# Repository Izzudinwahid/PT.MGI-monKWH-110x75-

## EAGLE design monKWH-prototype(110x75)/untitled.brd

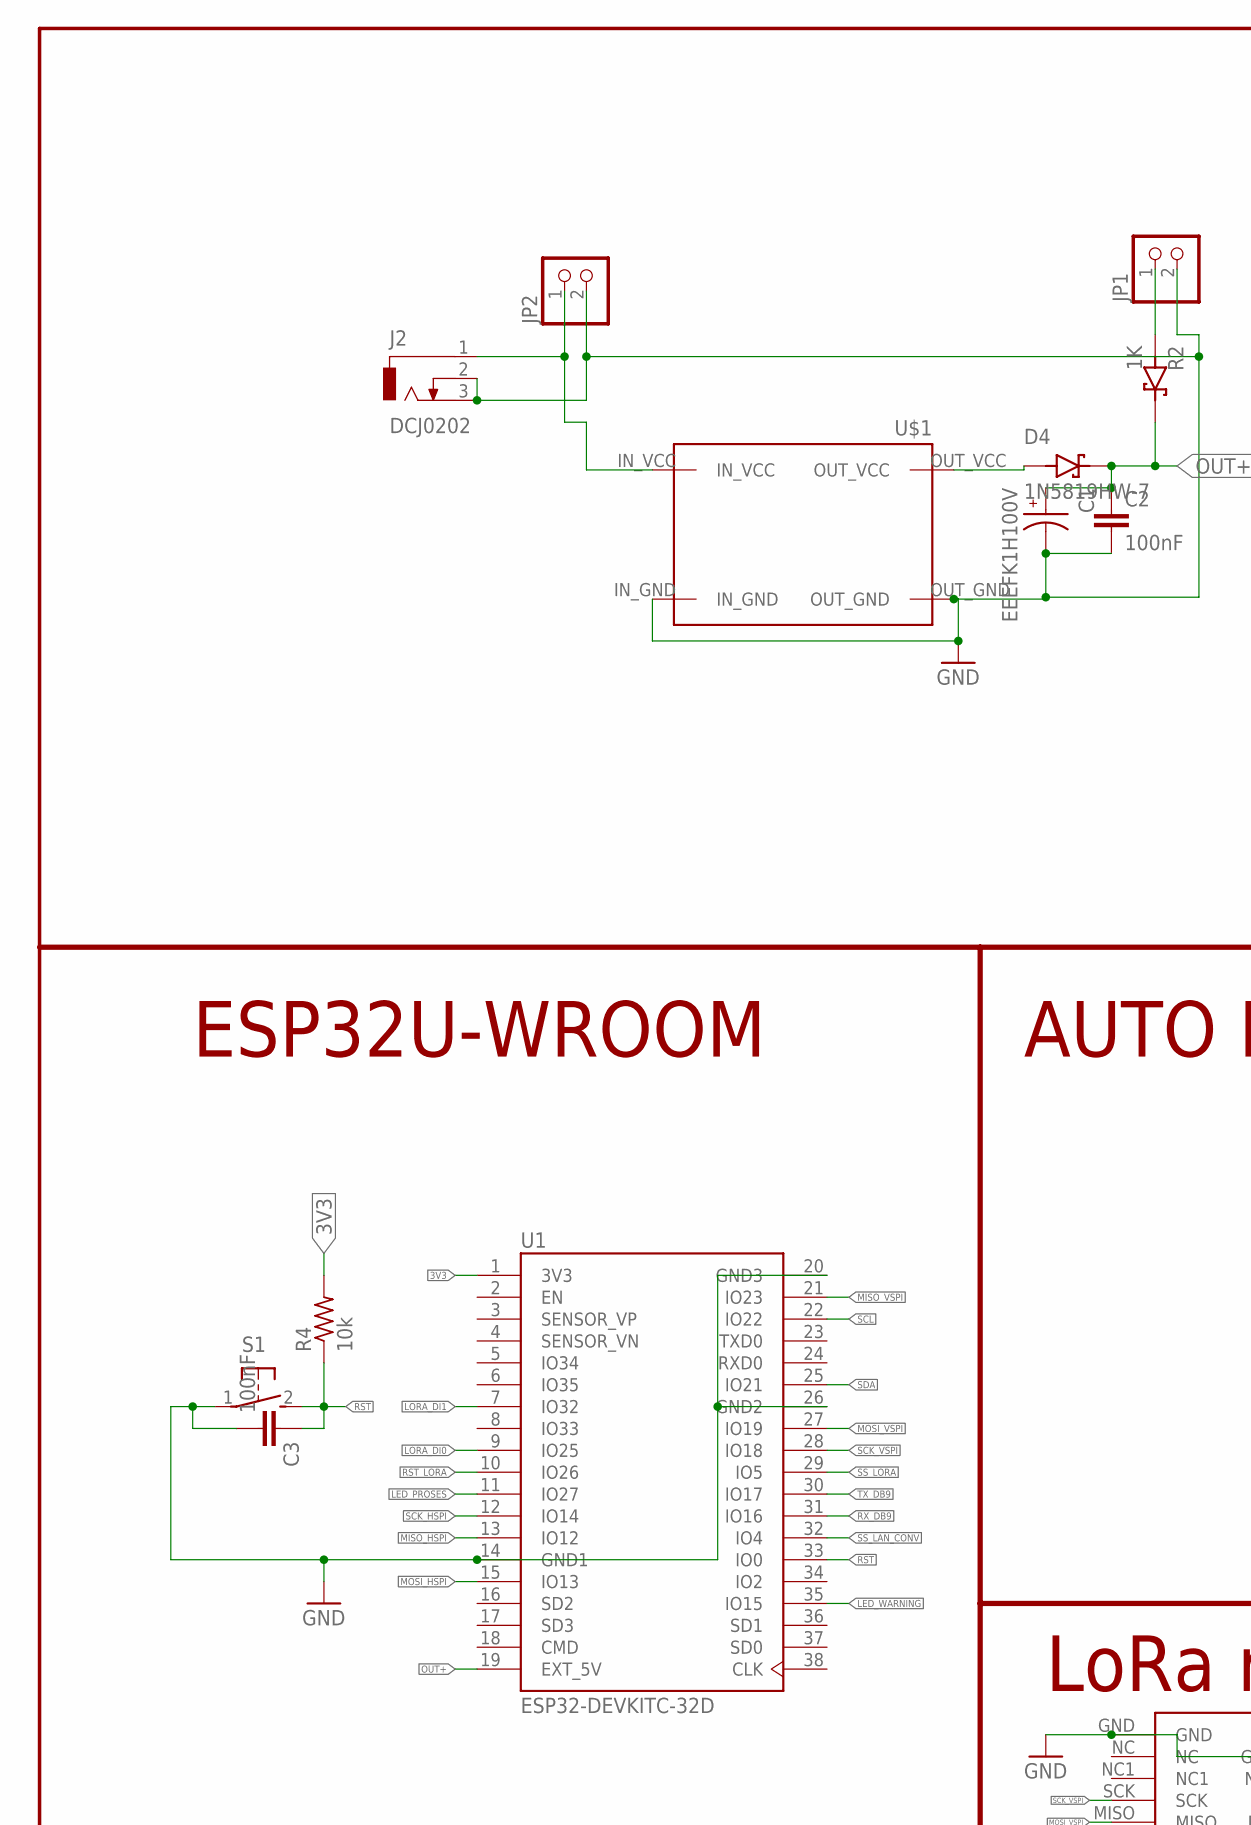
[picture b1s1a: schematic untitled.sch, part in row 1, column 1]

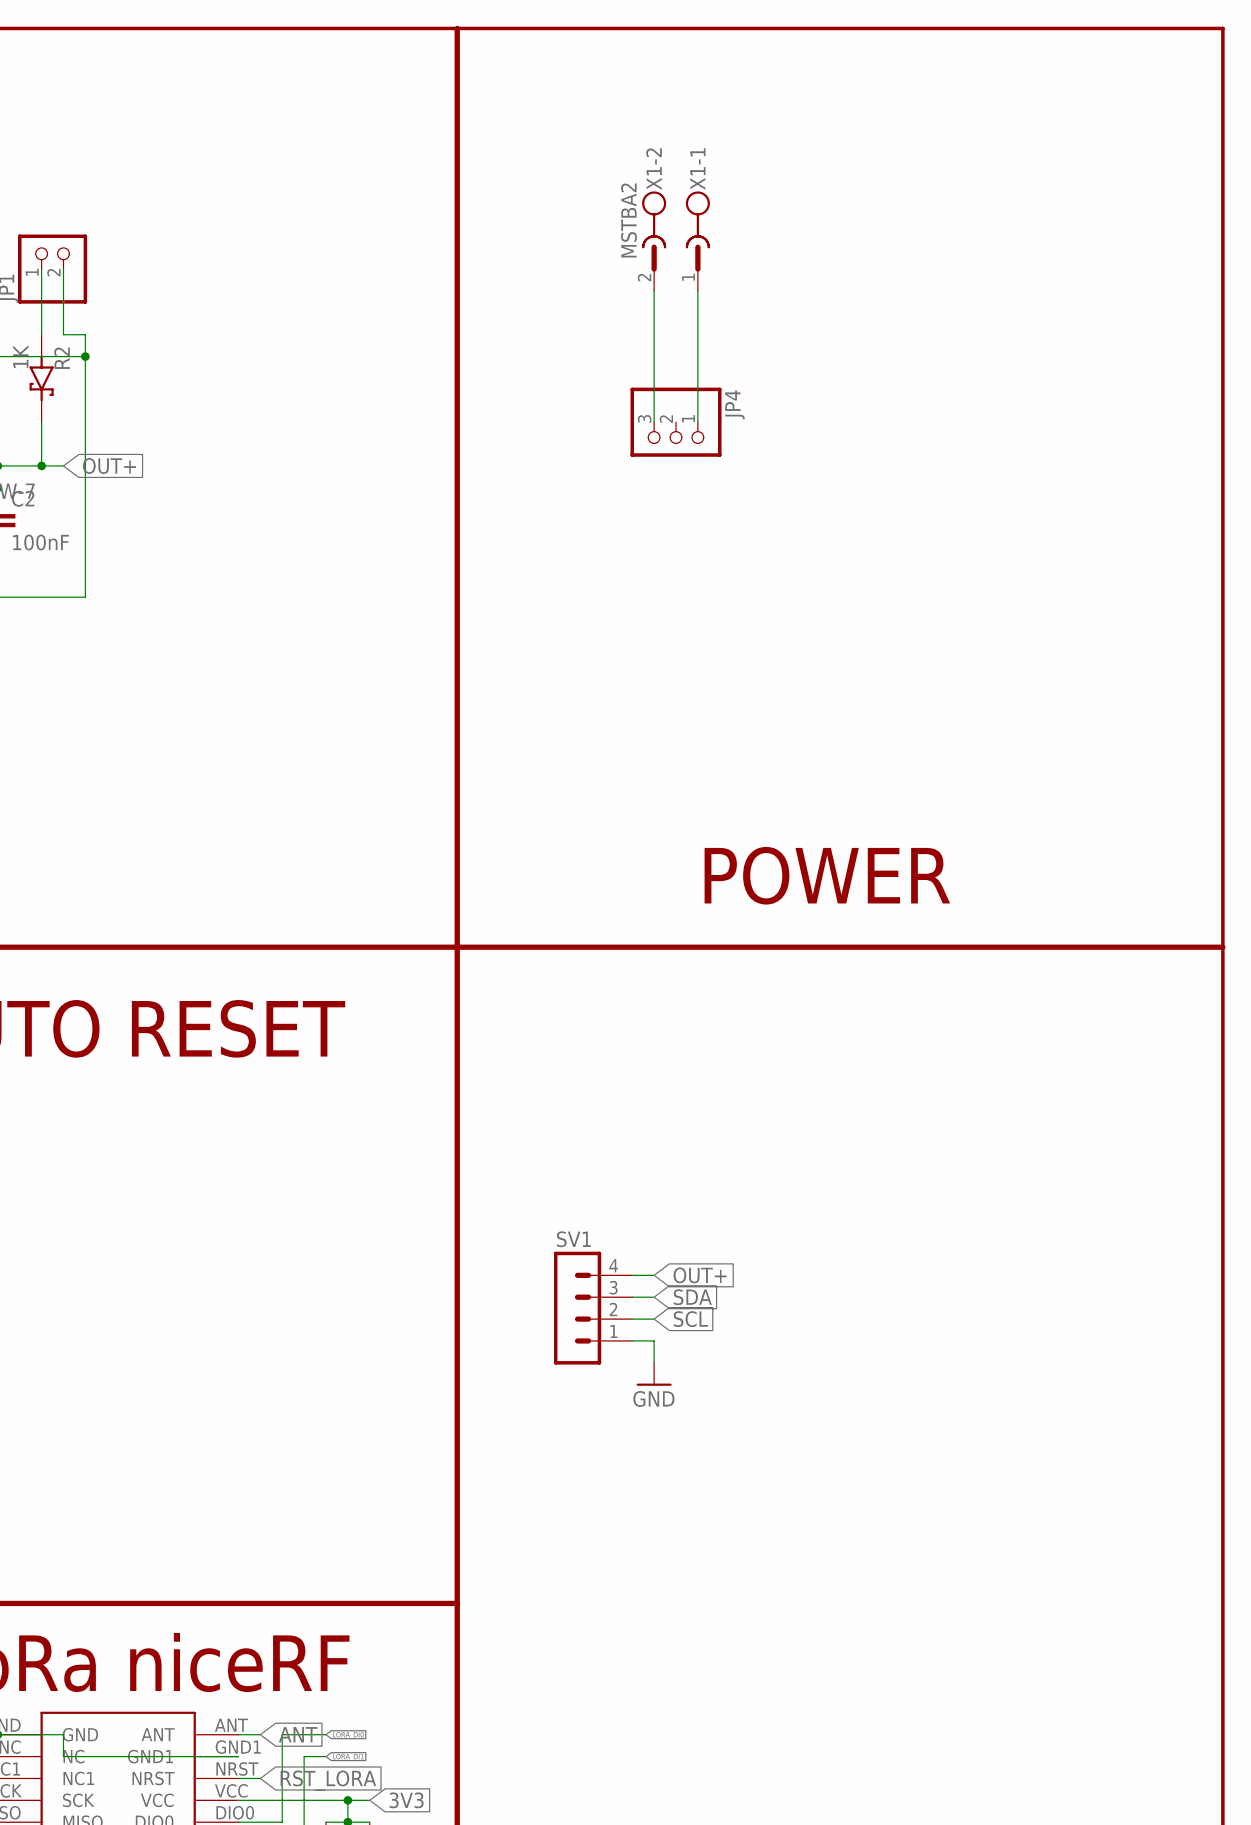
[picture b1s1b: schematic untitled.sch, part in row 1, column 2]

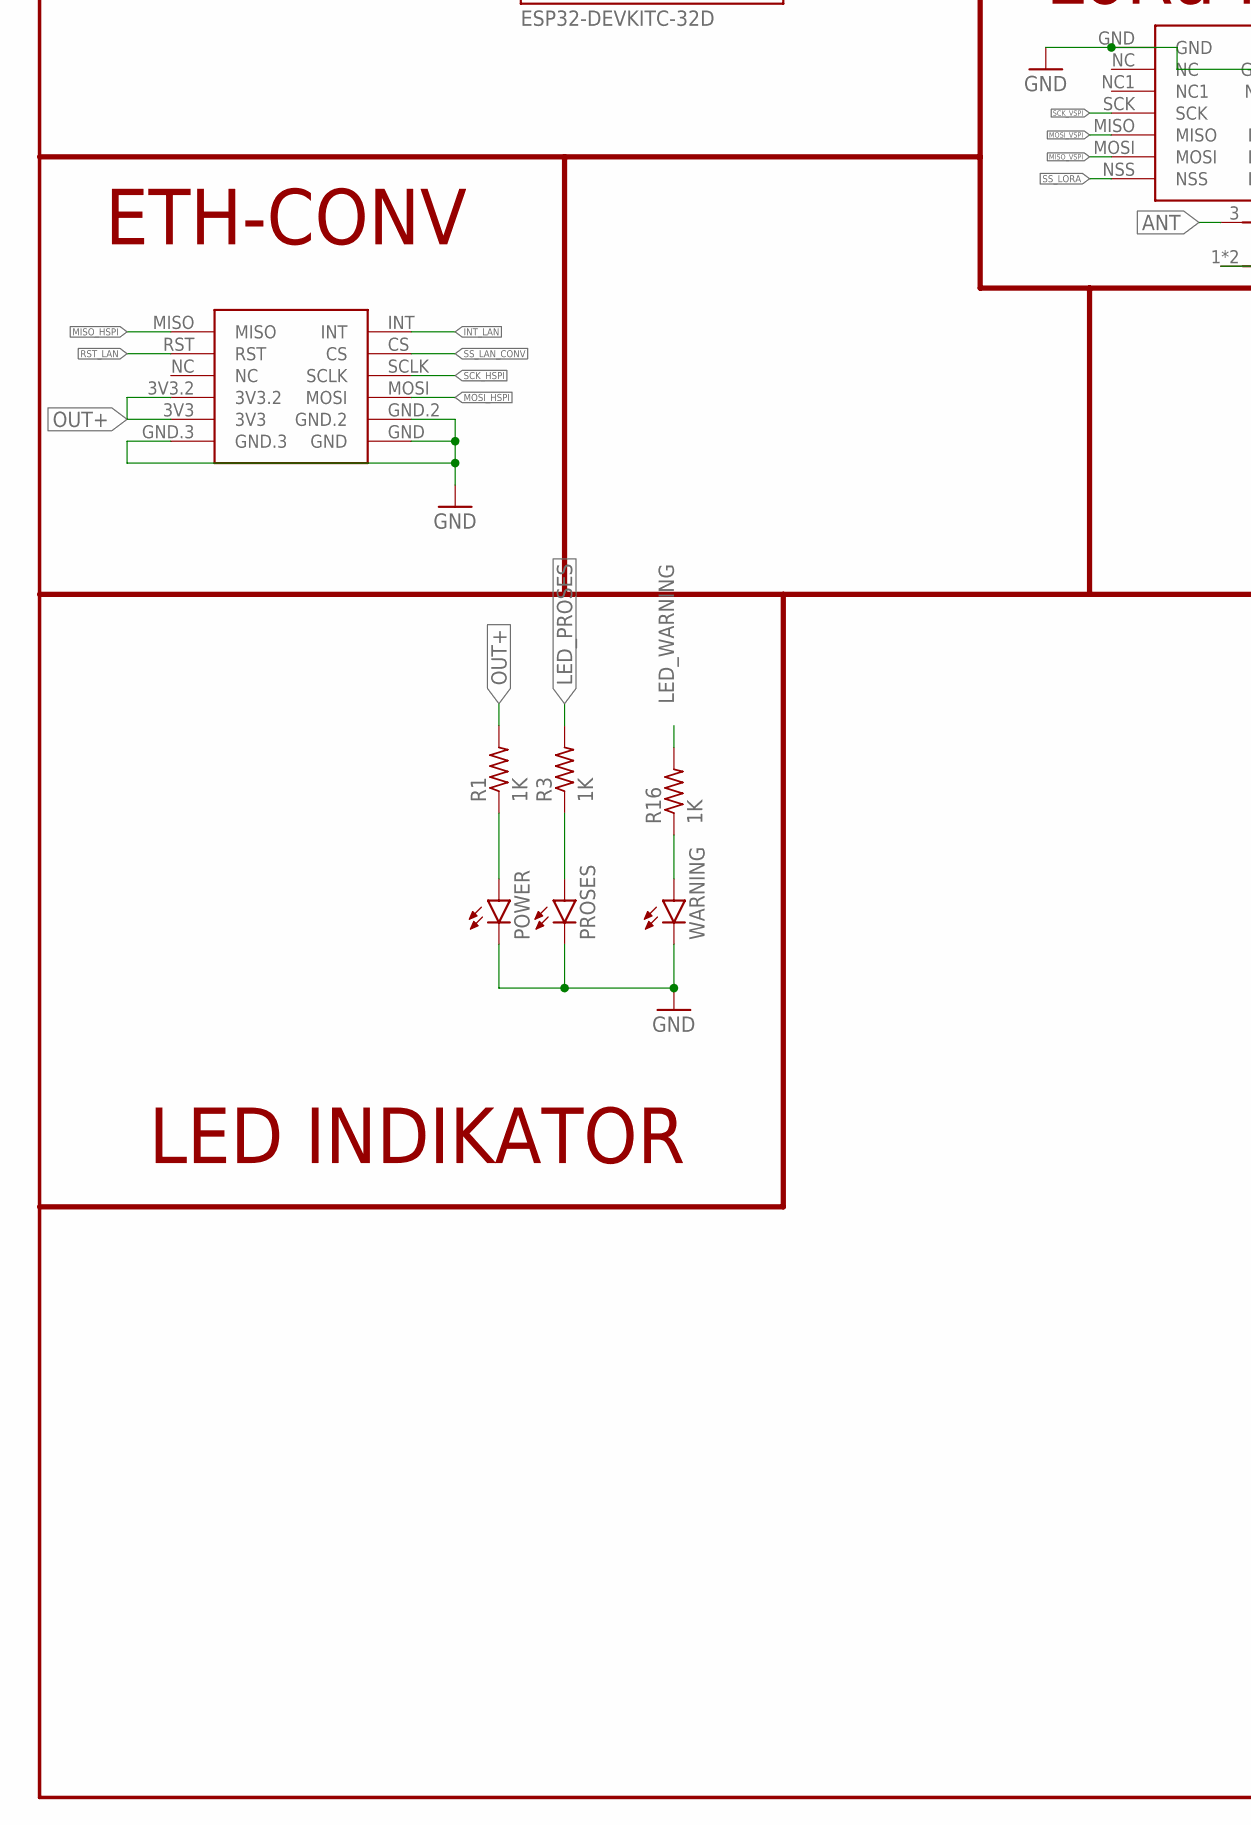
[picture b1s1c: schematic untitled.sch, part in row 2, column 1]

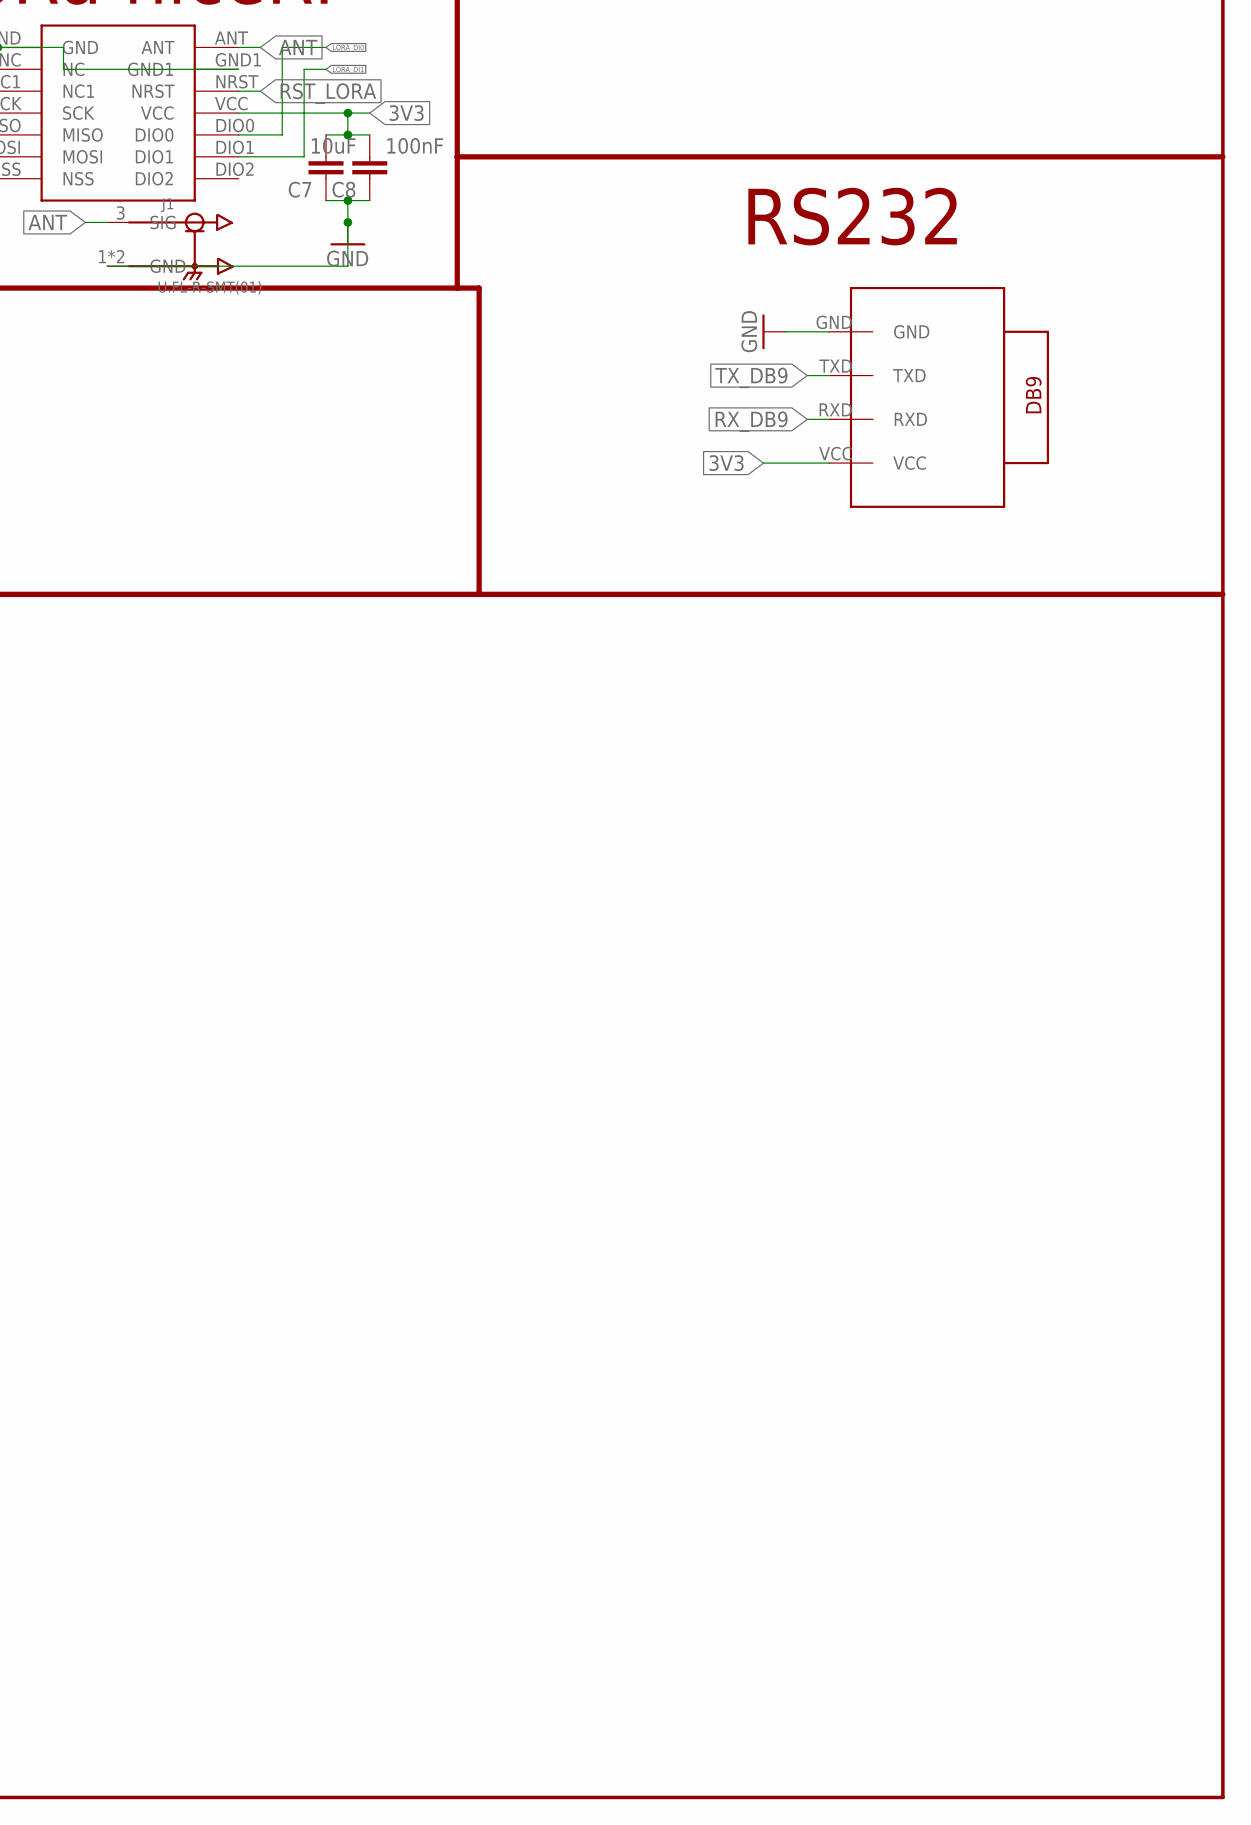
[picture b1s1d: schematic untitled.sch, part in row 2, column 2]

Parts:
C1: EEEFK1H100V; CAP_EEEFK1H100V
C2, C3, C8: 100nF; C0805K
C7: 10uF; C0805K
D4: 1N5819HW-7; SOD3715X145N
J1: U.FL-R-SMT(01); HRS_U.FL-R-SMT(01)
J2: DCJ0202
JP1, JP2: PINHD-1X2; 1X02
JP4: PINHD-1X3; 1X03
LORA-NICERF-V1: LORA-NICERF-V2
POWER: TLLR4400; LED3MM
PROSES: TLLR4400; LED3MM
R1, R3, R16: 1K; M0805
R2: 1K; SOD3715X145N
R4: 10k; M0805
S1: 31-XX; B3F-31XX
SV1: MA04-1
U1: ESP32-DEVKITC-32D; MODULE_ESP32-DEVKITC-32D
U$1: STEPDOWN_SY8205
U$3: MINI_W5500
U$5: RS232-BREAKOUTBREAKOUT; RS232-BREAKOUT
WARNING: TLLR4400; LED3MM
X1: MSTBA2

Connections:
3V3: C7.2, C8.2, LORA-NICERF-V1.VCC, R4.2, U1.1 (3V3), U$5.VCC
ANT: J1.3 (SIG), LORA-NICERF-V1.ANT
GND: C1.2, C2.2, C3.2, C7.1, C8.1, J1.1 (GND), J1.2 (GND), J2.2, J2.3, JP1.2, JP2.2, LORA-NICERF-V1.GND, LORA-NICERF-V1.GND1, POWER.K (C), PROSES.K (C), S1.1, SV1.1, U1.14 (GND1), U1.20 (GND3), U1.26 (GND2), U$1.IN_GND, U$1.OUT_GND, U$3.GND, U$3.GND.2, U$3.GND.3, U$5.GND, WARNING.K (C)
INT_LAN: U$3.INT
LED_PROSES: R3.2, U1.11 (IO27)
LED_WARNING: R16.2, U1.35 (IO15)
LORA_DI0: LORA-NICERF-V1.DIO0, U1.9 (IO25)
LORA_DI1: LORA-NICERF-V1.DIO1, U1.7 (IO32)
MISO_HSPI: U1.13 (IO12), U$3.MISO
MISO_VSPI: LORA-NICERF-V1.MOSI, U1.21 (IO23)
MOSI_HSPI: U1.15 (IO13), U$3.MOSI
MOSI_VSPI: LORA-NICERF-V1.MISO, U1.27 (IO19)
unnamed: POWER.A, R1.1
unnamed: PROSES.A, R3.1
unnamed: J2.1, JP2.1, U$1.IN_VCC
unnamed: JP4.3, X1.2
unnamed: D4.A, U$1.OUT_VCC
unnamed: JP1.1, R2.A
unnamed: JP4.1, X1.1
unnamed: R16.1, WARNING.A
OUT+: C1.1, C2.1, D4.C (K), R1.2, R2.C (K), SV1.4, U1.19 (EXT_5V), U$3.3V3, U$3.3V3.2
RST: C3.1, R4.1, S1.2 (S), U1.33 (IO0)
RST_LAN: U$3.RST
RST_LORA: LORA-NICERF-V1.NRST, U1.10 (IO26)
RX_DB9: U1.31 (IO16), U$5.RXD
SCK_HSPI: U1.12 (IO14), U$3.SCLK
SCK_VSPI: LORA-NICERF-V1.SCK, U1.28 (IO18)
SCL: SV1.2, U1.22 (IO22)
SDA: SV1.3, U1.25 (IO21)
SS_LAN_CONV: U1.32 (IO4), U$3.CS
SS_LORA: LORA-NICERF-V1.NSS, U1.29 (IO5)
TX_DB9: U1.30 (IO17), U$5.TXD

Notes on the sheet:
POWER
ESP32U-WROOM
AUTO RESET
LoRa niceRF
ETH-CONV
RS232
LED INDIKATOR

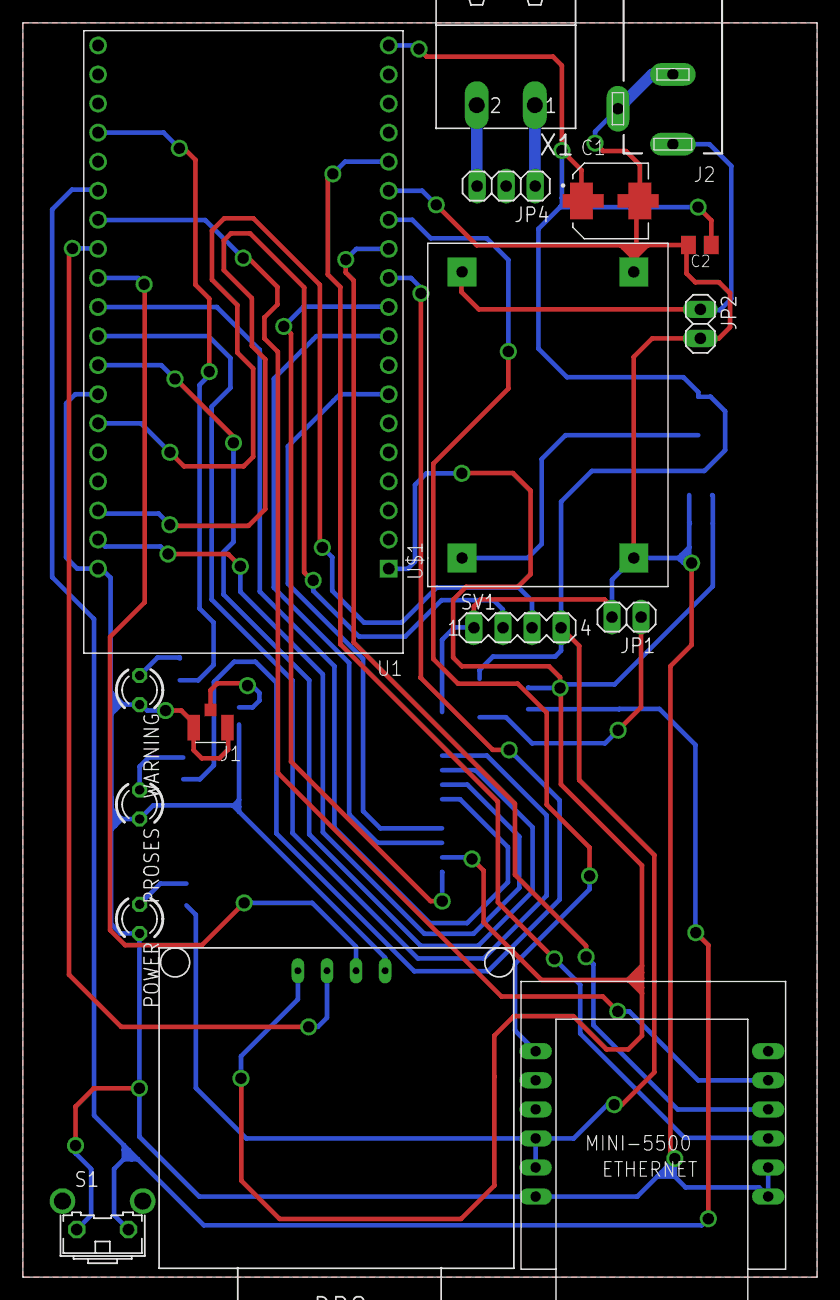
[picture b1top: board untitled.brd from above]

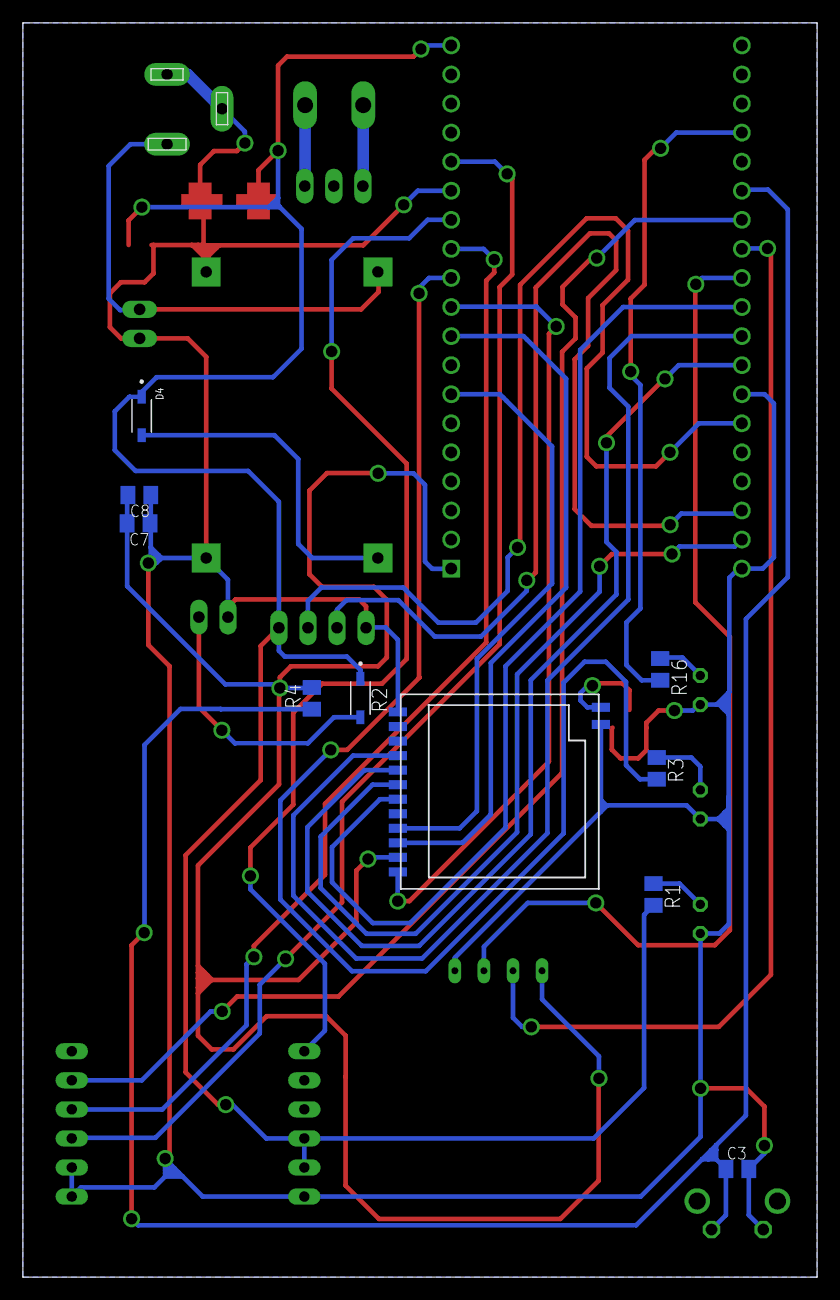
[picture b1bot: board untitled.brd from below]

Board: 2 copper layers, 69.4 x 109.6 mm, 27 parts (10 on the bottom side), 30 nets.

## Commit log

2022-08-23 file PCB
2022-08-23 menambahkan komponen coaxial conn
2022-08-23 revisi footprint LoRa
2022-08-25 mengubah board
2022-08-25 revisi .brd
2022-08-25 revisi dimensi
2022-09-07 perubahan mikro dan penambahan Jack-DC
2022-09-07 revisi jaulur .brd
